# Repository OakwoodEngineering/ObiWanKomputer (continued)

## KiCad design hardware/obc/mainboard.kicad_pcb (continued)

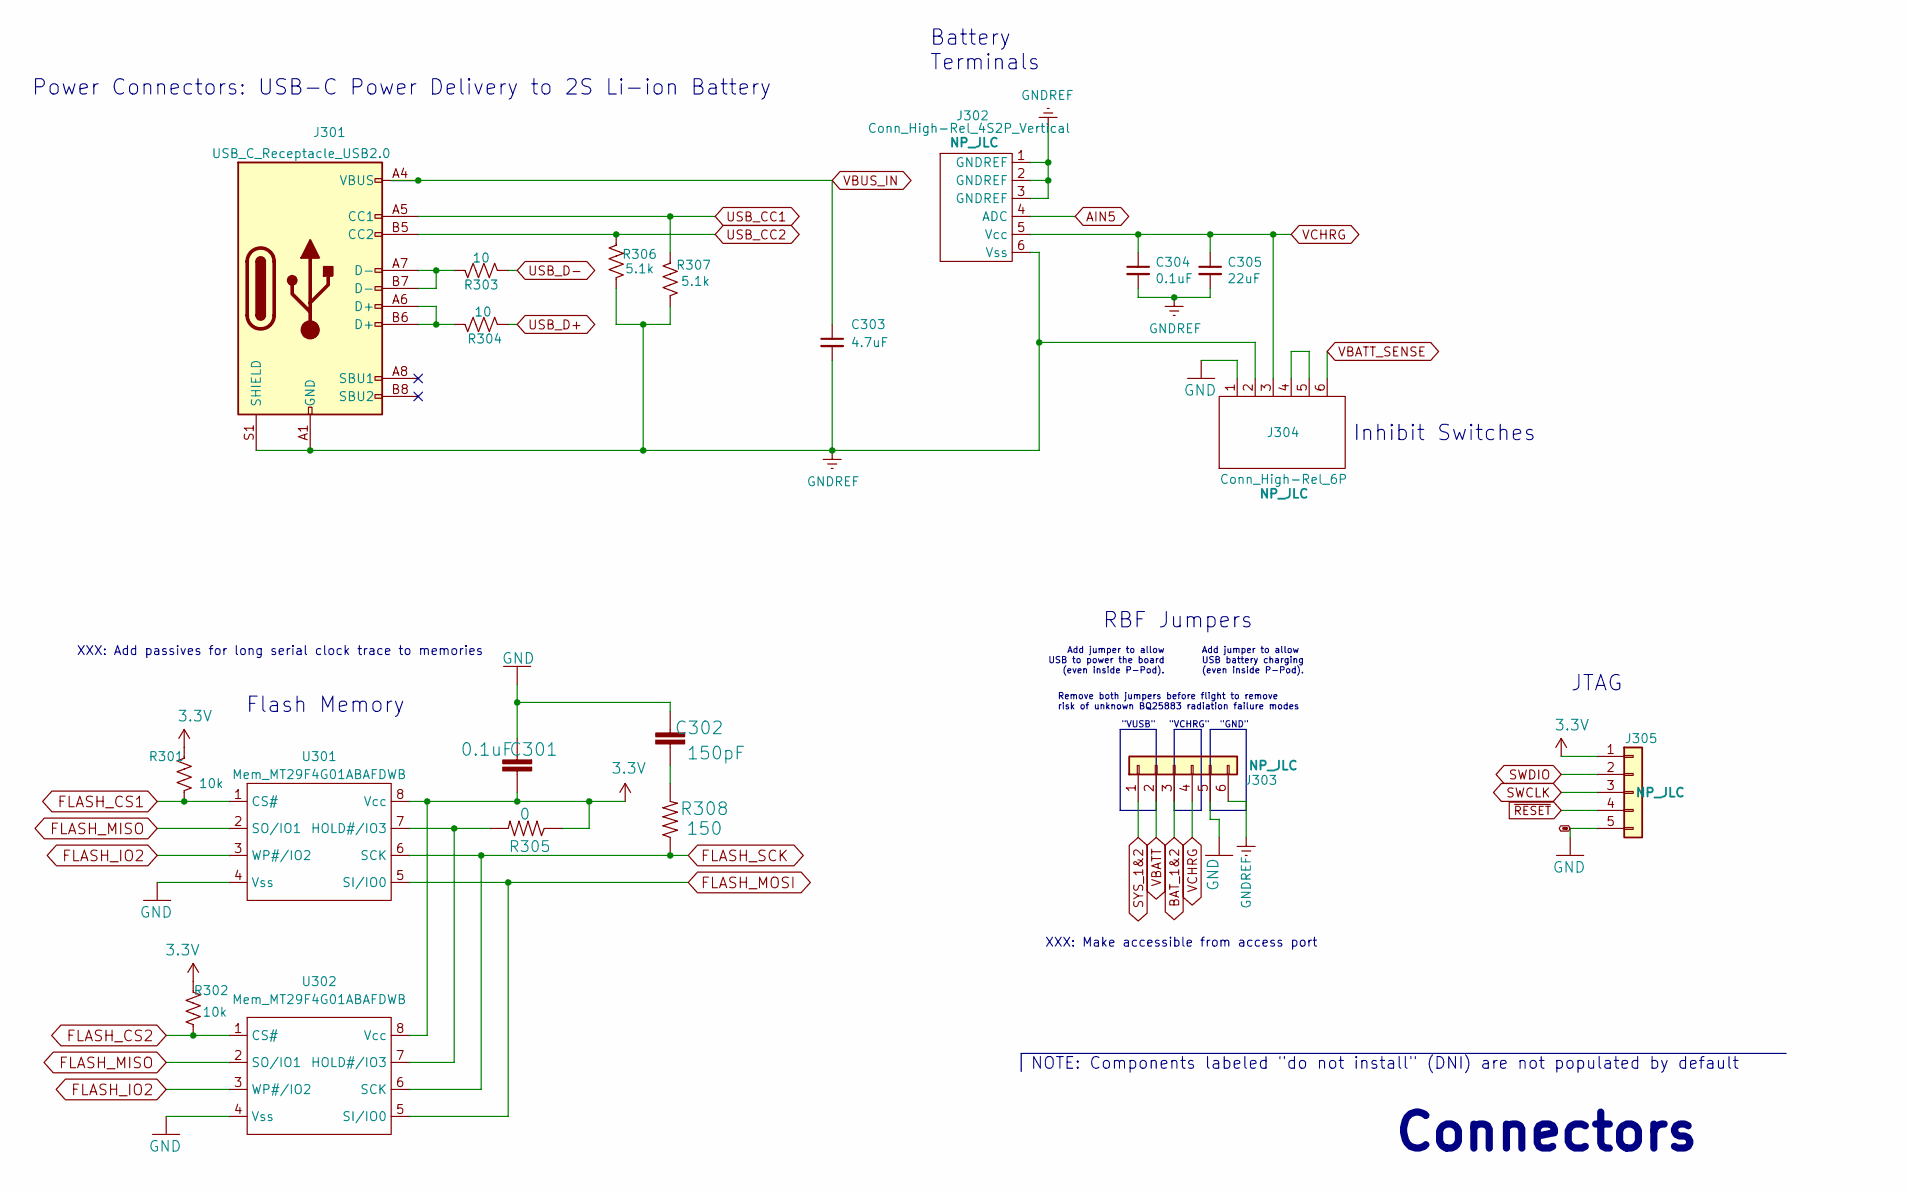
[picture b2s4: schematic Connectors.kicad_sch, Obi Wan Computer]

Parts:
C301, C304: 0.1uF; C_0603_1608Metric; Manufacturer_Part_Number CL10B104KB8NNNC; LCSC C1591
C302: 150pF; C_0603_1608Metric; Manufacturer_Part_Number CC0603JRNPO9BN151; LCSC C107038
C303: 4.7uF; C_0603_1608Metric; Manufacturer_Part_Number CL10A475KP8NNNC; LCSC C1705
C305: 22uF; C_0603_1608Metric; Manufacturer_Part_Number GRM188R61A226ME15D; LCSC C84419
J301: USB_C_Receptacle_USB2.0; USB_C_Receptacle_G-Switch_GT-USB-7010ASV; Manufacturer_Part_Number GT-USB-7010ASV; LCSC C2988369
J302: Conn_High-Rel_4S2P_Vertical; Harwin_G125-FV104F3-02AB000P_P1.25mm_Vertical; Manufacturer_Part_Number G125-FV104F3-02AB000P
J303: Conn_01x06; PinHeader_1x06_P2.54mm_Horizontal
J304: Conn_High-Rel_6P; MMCX-6_UMPT-06-01-L-RA-WT-TR_P2.0mm; Manufacturer_Part_Number UMPT-06-01-L-RA-WT-TR
J305: Conn_01x05; PinHeader_1x05_P2.54mm_Vertical
R301, R302: 10k; R_0603_1608Metric; Manufacturer_Part_Number ERJ3GEYJ103V; LCSC C169849
R303, R304: 10; R_0603_1608Metric; Manufacturer_Part_Number AC0603FR-0710RL; LCSC C138286
R305: 0; R_0603_1608Metric; Manufacturer_Part_Number MCT06030Z0000ZP500; LCSC C2654002
R306, R307: 5.1k; R_0603_1608Metric; Manufacturer_Part_Number RC0603FR-075K1L; LCSC C105580
R308: 150; R_0603_1608Metric; Manufacturer_Part_Number ERJ3RBD1500V; LCSC C336847
U301, U302: Mem_MT29F4G01ABAFDWB; UPDFN-8_8.0x6.0mm_P1.27mm; Manufacturer_Part_Number MT29F4G01ABAFDWB-IT:F; LCSC C2909506

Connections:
3.3V: C301.1, J305.1, R301.2, R302.2, R305.1, U301.8 (Vcc), U302.8 (Vcc); also elsewhere on the board
AIN5: J302.4 (ADC); also elsewhere on the board
BAT_1&2: J303.3; also elsewhere on the board
FLASH_CS1: R301.1, U301.1 (CS#); also elsewhere on the board
FLASH_CS2: R302.1, U302.1 (CS#); also elsewhere on the board
FLASH_IO2: U301.3 (WP#/IO2), U302.3 (WP#/IO2); also elsewhere on the board
FLASH_MISO: U301.2 (SO/IO1), U302.2 (SO/IO1); also elsewhere on the board
FLASH_MOSI: U301.5 (SI/IO0), U302.5 (SI/IO0); also elsewhere on the board
FLASH_SCK: R308.1, U301.6 (SCK), U302.6 (SCK); also elsewhere on the board
GND: C301.2, C302.2, J303.5, J304.1, J305.5, U301.4 (Vss), U302.4 (Vss); also elsewhere on the board
GNDREF: C303.2, C304.2, C305.2, J301.A1 (GND), J301.A12 (GND), J301.B1 (GND), J301.B12 (GND), J301.S1 (SHIELD), J302.1 (GNDREF), J302.2 (GNDREF), J302.3 (GNDREF), J302.6 (Vss), J303.6, J304.2, R306.1, R307.1; also elsewhere on the board
unnamed: C302.1, R308.2
unnamed: J301.A6 (D+), J301.B6 (D+), R304.2
unnamed: J301.A7 (D-), J301.B7 (D-), R303.2
unnamed: J304.4, J304.5
unnamed: R305.2, U301.7 (HOLD#/IO3), U302.7 (HOLD#/IO3)
SWCLK: J305.3; also elsewhere on the board
SWDIO: J305.2; also elsewhere on the board
SYS_1&2: J303.1; also elsewhere on the board
USB_CC1: J301.A5 (CC1), R307.2
USB_CC2: J301.B5 (CC2), R306.2
USB_D+: R304.1; also elsewhere on the board
USB_D-: R303.1; also elsewhere on the board
VBATT: J303.2; also elsewhere on the board
VBATT_SENSE: J304.6; also elsewhere on the board
VBUS_IN: C303.1, J301.A4 (VBUS), J301.A9 (VBUS), J301.B4 (VBUS), J301.B9 (VBUS); also elsewhere on the board
VCHRG: C304.1, C305.1, J302.5 (Vcc), J303.4, J304.3
~RESET: J305.4; also elsewhere on the board

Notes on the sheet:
NOTE: Components labeled "do not install" (DNI) are not populated by default
XXX: Add passives for long serial clock trace to memories
Add jumper to allow USB battery charging (even inside P-Pod).
Remove both jumpers before flight to remove risk of unknown BQ25883 radiation failure modes
Connectors
Flash Memory
Battery Terminals
"VCHRG"
XXX: Make accessible from access port
RBF Jumpers
Power Connectors: USB-C Power Delivery to 2S Li-ion Battery
"GND"
Inhibit Switches
Add jumper to allow USB to power the board (even inside P-Pod).
"VUSB"
JTAG

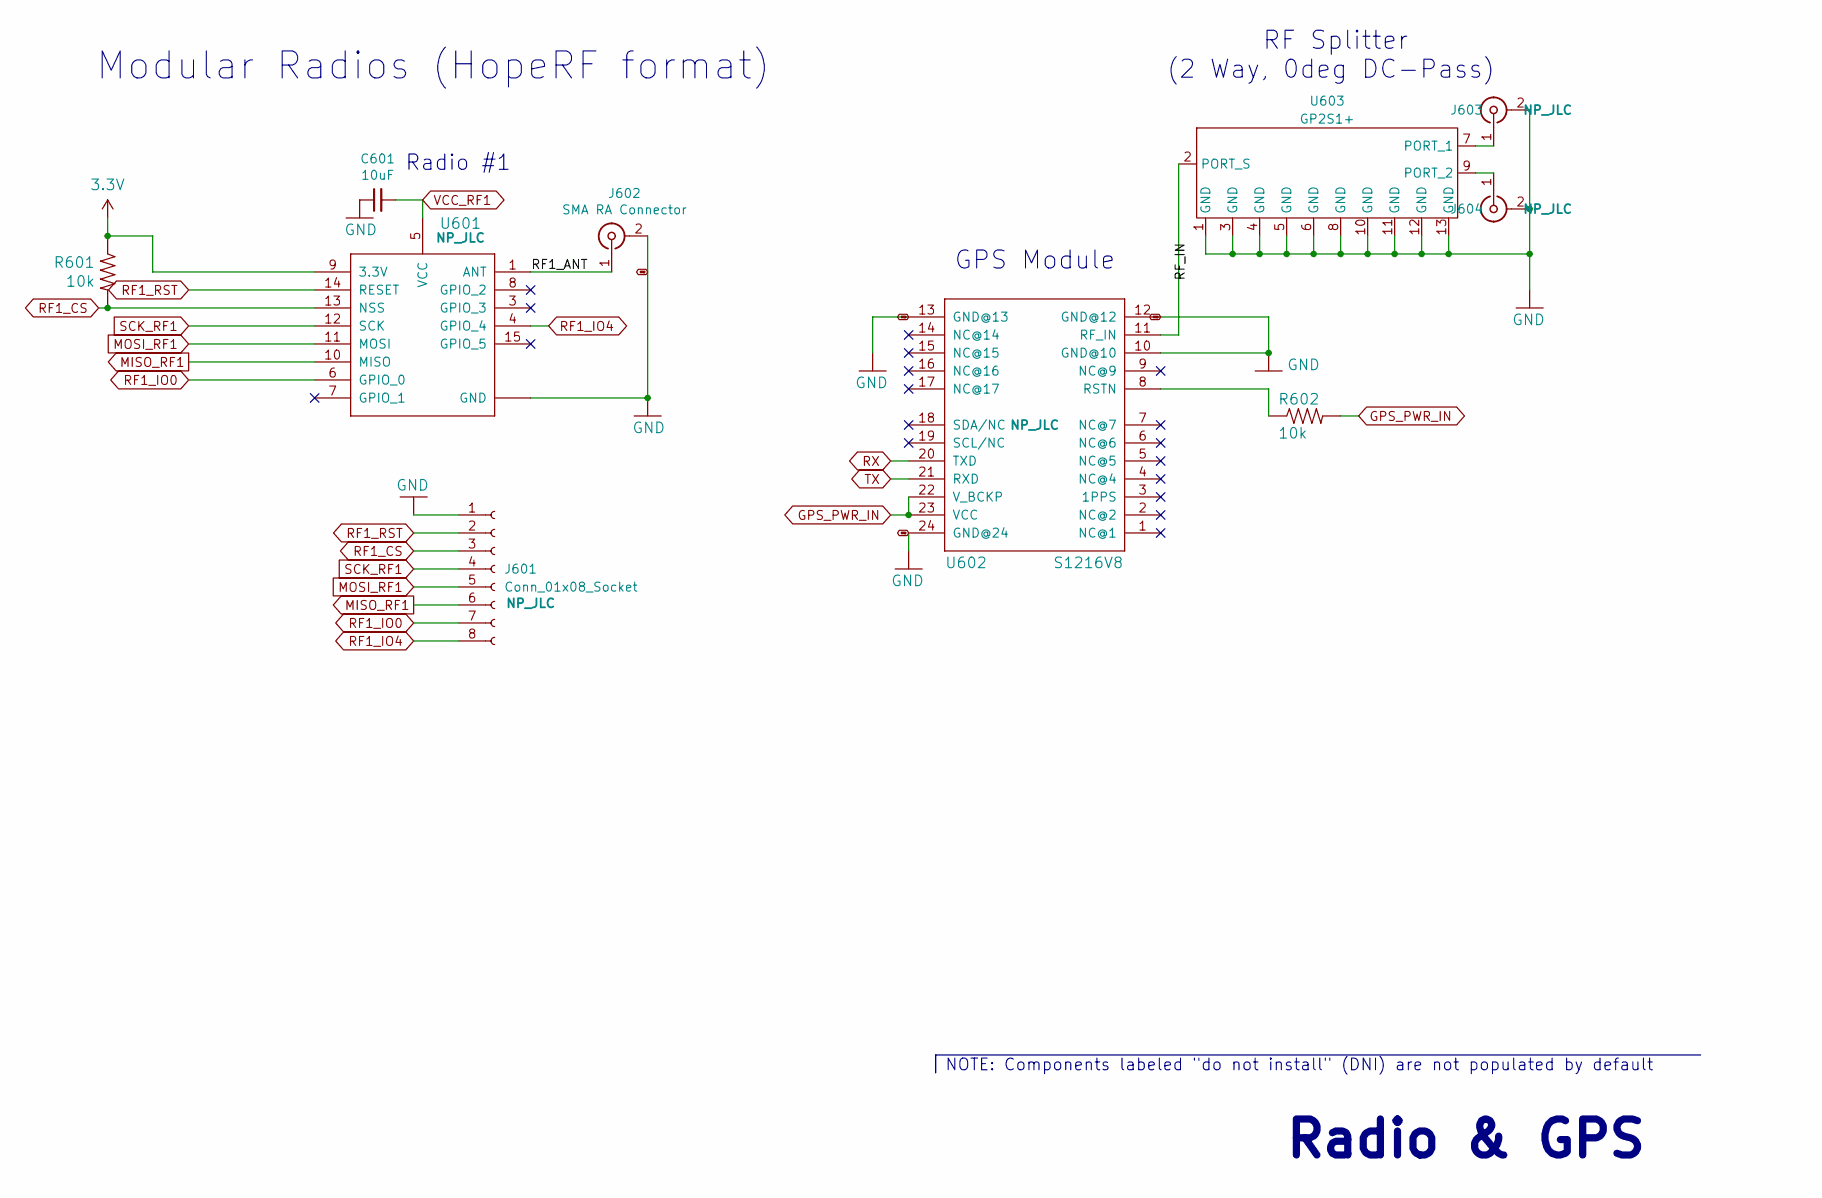
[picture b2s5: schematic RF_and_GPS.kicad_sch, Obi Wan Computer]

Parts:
C601: 10uF; C_0603_1608Metric; Manufacturer_Part_Number CL10A106MP8NNNC; LCSC C85713
J601: Conn_01x08_Socket; PinSocket_1x08_P2.54mm_Vertical
J602, J603, J604: SMA RA Connector; SAMTEC_MMCXV-J-P-HF-ST-EM1; Manufacturer_Part_Number MMCXV-J-P-HF-ST-EM1-ND
R601, R602: 10k; R_0603_1608Metric; Manufacturer_Part_Number ERJ3GEYJ103V; LCSC C169849
U601: RFM98PW; RFM95PW; Manufacturer_Part_Number RFM98PW
U602: S1216V8; S1216_24PIN_PACKAGE; Manufacturer_Part_Number S1216V8
U603: GP2S1+; DQ1225-12-1EP_3.0x3.0mm_P0.51mm; Manufacturer_Part_Number GP2S1+; LCSC C879828

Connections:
3.3V: R601.1, U601.9 (3.3V); also elsewhere on the board
/RF and GPS/RF1_ANT: J602.1 (In), U601.1 (ANT)
GND: C601.1, J601.1, J602.2 (Ext), J603.2 (Ext), J604.2 (Ext), U601.2 (GND), U601.16 (GND), U601.17 (GND), U602.10 (GND@10), U602.12 (GND@12), U602.13 (GND@13), U602.24 (GND@24), U603.1 (GND), U603.3 (GND), U603.4 (GND), U603.5 (GND), U603.6 (GND), U603.8 (GND), U603.10 (GND), U603.11 (GND), U603.12 (GND), U603.13 (GND); also elsewhere on the board
GPS_PWR_IN: R602.2, U602.22 (V_BCKP), U602.23 (VCC); also elsewhere on the board
MISO_RF1: J601.6, U601.10 (MISO); also elsewhere on the board
MOSI_RF1: J601.5, U601.11 (MOSI); also elsewhere on the board
unnamed: J603.1 (In), U603.7 (PORT_1)
unnamed: J604.1 (In), U603.9 (PORT_2)
unnamed: U602.11 (RF_IN), U603.2 (PORT_S)
unnamed: R602.1, U602.8 (RSTN)
RF1_CS: J601.3, R601.2, U601.13 (NSS); also elsewhere on the board
RF1_IO0: J601.7, U601.6 (GPIO_0); also elsewhere on the board
RF1_IO4: J601.8, U601.4 (GPIO_4); also elsewhere on the board
RF1_RST: J601.2, U601.14 (RESET); also elsewhere on the board
RX: U602.20 (TXD); also elsewhere on the board
SCK_RF1: J601.4, U601.12 (SCK); also elsewhere on the board
TX: U602.21 (RXD); also elsewhere on the board
VCC_RF1: C601.2, U601.5 (VCC); also elsewhere on the board

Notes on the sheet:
RF Splitter (2 Way, 0deg DC-Pass)
Modular Radios (HopeRF format)
Radio & GPS
NOTE: Components labeled "do not install" (DNI) are not populated by default
Radio #1
GPS Module

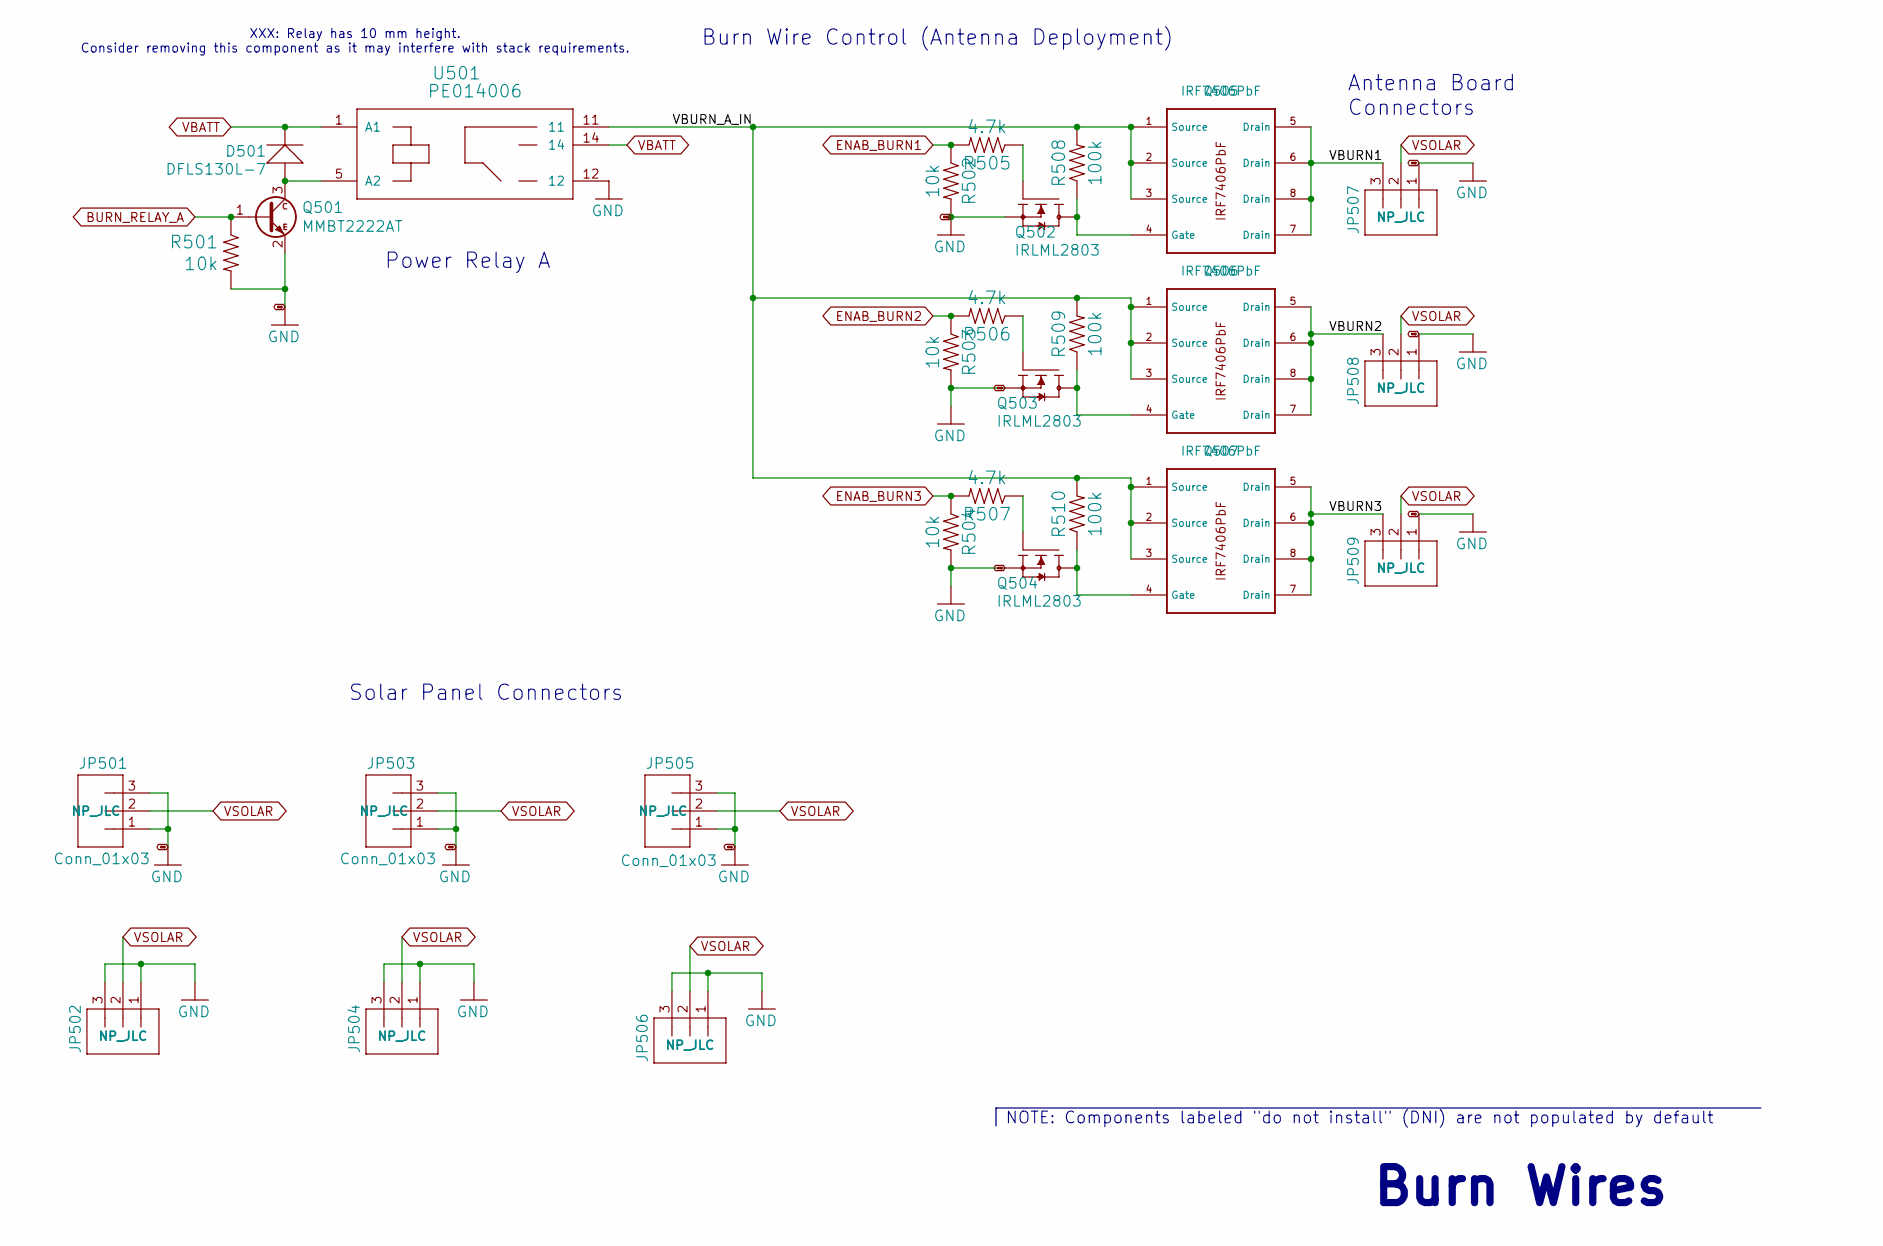
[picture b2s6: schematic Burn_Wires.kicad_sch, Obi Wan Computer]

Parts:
D501: DFLS130L-7; D_SOD-123; Manufacturer_Part_Number DFLS130L-7; LCSC C110493
JP501, JP502, JP503, JP504, JP505, JP506, JP507, JP508, JP509: Conn_01x03; CONN_22-11-2032_MOL; Manufacturer_Part_Number 0022112032
Q501: MMBT2222AT; SOT-23; Manufacturer_Part_Number MMBT2222ALT1G; LCSC C82460
Q502, Q503, Q504: IRLML2803; SOT-23; Manufacturer_Part_Number IRLML2803TRPBF; LCSC C2590
Q505, Q506, Q507: IRF7406PbF; SO-8_3.9x4.9mm_P1.27mm; Manufacturer_Part_Number IRF7406TRPBF; LCSC C169769
R501, R502, R503, R504: 10k; R_0603_1608Metric; Manufacturer_Part_Number ERJ3GEYJ103V; LCSC C169849
R505, R506, R507: 4.7k; R_0603_1608Metric; Manufacturer_Part_Number 0603WAF4701T5E; LCSC C23162
R508, R509, R510: 100k; R_0603_1608Metric; Manufacturer_Part_Number CRCW0603100KFKEC; LCSC C5369222
U501: PE014006; RELAY_PE014006_REV-SSE; Manufacturer_Part_Number PE014006 TE

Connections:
/Burn Wires/VBURN1: JP507.3, Q505.5 (Drain), Q505.6 (Drain), Q505.7 (Drain), Q505.8 (Drain)
/Burn Wires/VBURN2: JP508.3, Q506.5 (Drain), Q506.6 (Drain), Q506.7 (Drain), Q506.8 (Drain)
/Burn Wires/VBURN3: JP509.3, Q507.5 (Drain), Q507.6 (Drain), Q507.7 (Drain), Q507.8 (Drain)
/Burn Wires/VBURN_A_IN: Q505.1 (Source), Q505.2 (Source), Q505.3 (Source), Q506.1 (Source), Q506.2 (Source), Q506.3 (Source), Q507.1 (Source), Q507.2 (Source), Q507.3 (Source), R508.2, R509.2, R510.2, U501.11
BURN_RELAY_A: Q501.1 (B), R501.1; also elsewhere on the board
ENAB_BURN1: R502.1, R505.2; also elsewhere on the board
ENAB_BURN2: R503.1, R506.2; also elsewhere on the board
ENAB_BURN3: R504.1, R507.2; also elsewhere on the board
GND: JP501.1, JP501.3, JP502.1, JP502.3, JP503.1, JP503.3, JP504.1, JP504.3, JP505.1, JP505.3, JP506.1, JP506.3, JP507.1, JP508.1, JP509.1, Q501.2 (E), Q502.2 (S), Q503.2 (S), Q504.2 (S), R501.2, R502.2, R503.2, R504.2, U501.12; also elsewhere on the board
unnamed: D501.A, Q501.3 (C), U501.5 (A2)
unnamed: Q502.3 (D), Q505.4 (Gate), R508.1
unnamed: Q502.1 (G), R505.1
unnamed: Q503.3 (D), Q506.4 (Gate), R509.1
unnamed: Q503.1 (G), R506.1
unnamed: Q504.3 (D), Q507.4 (Gate), R510.1
unnamed: Q504.1 (G), R507.1
VBATT: D501.C, U501.1 (A1), U501.14; also elsewhere on the board
VSOLAR: JP501.2, JP502.2, JP503.2, JP504.2, JP505.2, JP506.2, JP507.2, JP508.2, JP509.2; also elsewhere on the board

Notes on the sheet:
Antenna Board Connectors
Burn Wires
XXX: Relay has 10 mm height. Consider removing this component as it may interfere with stack requirements.
Burn Wire Control (Antenna Deployment)
Solar Panel Connectors
Power Relay A
NOTE: Components labeled "do not install" (DNI) are not populated by default

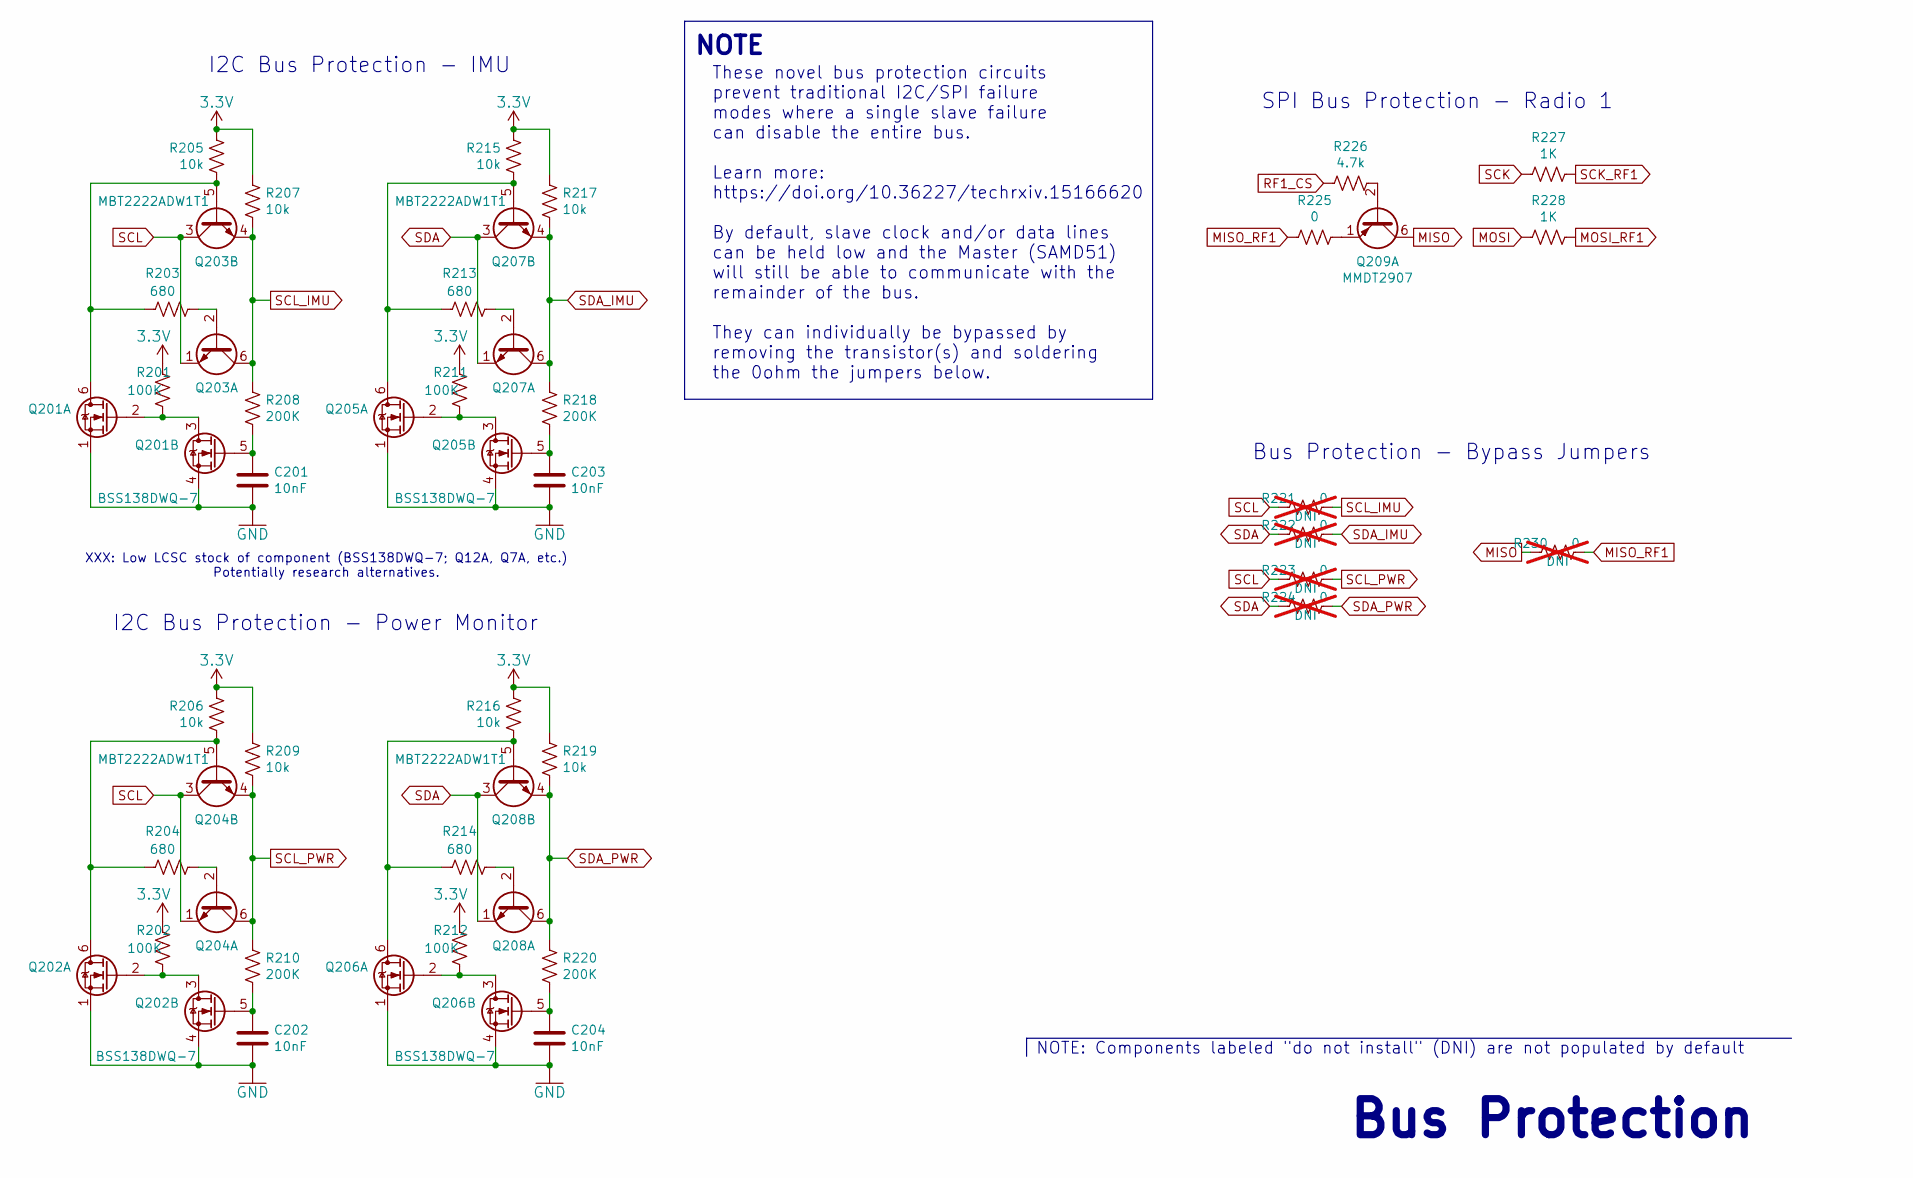
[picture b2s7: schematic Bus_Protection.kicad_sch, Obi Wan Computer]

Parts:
C201, C202, C203, C204: 10nF; C_0603_1608Metric; Manufacturer_Part_Number CL10B103KB8NNNC; LCSC C1589
Q201, Q202, Q205, Q206: BSS138DWQ-7; SOT-363_SC-70-6; Manufacturer_Part_Number BSS138DWQ-7; LCSC C3280240
Q203, Q204, Q207, Q208: MBT2222ADW1T1; SOT-363_SC-70-6; Manufacturer_Part_Number MBT2222ADW1T1G; LCSC C157366
Q209: MMDT2907; SOT-363_SC-70-6; Manufacturer_Part_Number MMDT2907AQ-7-F; LCSC C526684
R201, R202, R211, R212: 100K; R_0603_1608Metric; Manufacturer_Part_Number CRCW0603100KFKEC; LCSC C5369222
R203, R204, R213, R214: 680; R_0603_1608Metric; Manufacturer_Part_Number CRCW0603680RJNEA; LCSC C4244464
R205, R206, R207, R209, R215, R216, R217, R219: 10k; R_0603_1608Metric; Manufacturer_Part_Number ERJ3GEYJ103V; LCSC C169849
R208, R210, R218, R220: 200K; R_0603_1608Metric; Manufacturer_Part_Number ERA3AEB204V; LCSC C473261
R221, R222, R223, R224, R230: 0; R_0603_1608Metric; Manufacturer_Part_Number MCT06030Z0000ZP500; not fitted
R225: 0; R_0603_1608Metric; Manufacturer_Part_Number MCT06030Z0000ZP500; LCSC C2654002
R226: 4.7k; R_0603_1608Metric; Manufacturer_Part_Number 0603WAF4701T5E; LCSC C23162
R227, R228: 1K; R_0603_1608Metric; Manufacturer_Part_Number CRCW06031K00FKEAC; LCSC C844746

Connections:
3.3V: R201.1, R202.1, R205.1, R206.1, R207.1, R209.1, R211.1, R212.1, R215.1, R216.1, R217.1, R219.1; also elsewhere on the board
GND: C201.2, C202.2, C203.2, C204.2, Q201.1 (S2), Q201.4 (S1), Q202.1 (S2), Q202.4 (S1), Q205.1 (S2), Q205.4 (S1), Q206.1 (S2), Q206.4 (S1); also elsewhere on the board
MISO: Q209.6 (C1), R230.2; also elsewhere on the board
MISO_RF1: R225.2, R230.1; also elsewhere on the board
MOSI: R228.1; also elsewhere on the board
MOSI_RF1: R228.2; also elsewhere on the board
unnamed: Q201.6 (D1), Q203.5 (B2), R203.2, R205.2
unnamed: Q201.2 (G2), Q201.3 (D2), R201.2
unnamed: C201.1, Q201.5 (G1), R208.2
unnamed: Q202.6 (D1), Q204.5 (B2), R204.2, R206.2
unnamed: Q202.2 (G2), Q202.3 (D2), R202.2
unnamed: C202.1, Q202.5 (G1), R210.2
unnamed: Q203.2 (B1), R203.1
unnamed: Q204.2 (B1), R204.1
unnamed: Q205.6 (D1), Q207.5 (B2), R213.2, R215.2
unnamed: Q205.2 (G2), Q205.3 (D2), R211.2
unnamed: C203.1, Q205.5 (G1), R218.2
unnamed: Q206.6 (D1), Q208.5 (B2), R214.2, R216.2
unnamed: Q206.2 (G2), Q206.3 (D2), R212.2
unnamed: C204.1, Q206.5 (G1), R220.2
unnamed: Q207.2 (B1), R213.1
unnamed: Q208.2 (B1), R214.1
unnamed: Q209.2 (B1), R226.1
unnamed: Q209.1 (E1), R225.1
RF1_CS: R226.2; also elsewhere on the board
SCK: R227.2; also elsewhere on the board
SCK_RF1: R227.1; also elsewhere on the board
SCL: Q203.1 (E1), Q203.3 (C2), Q204.1 (E1), Q204.3 (C2), R221.2, R223.2; also elsewhere on the board
SCL_IMU: Q203.4 (E2), Q203.6 (C1), R207.2, R208.1, R221.1; also elsewhere on the board
SCL_PWR: Q204.4 (E2), Q204.6 (C1), R209.2, R210.1, R223.1; also elsewhere on the board
SDA: Q207.1 (E1), Q207.3 (C2), Q208.1 (E1), Q208.3 (C2), R222.2, R224.2; also elsewhere on the board
SDA_IMU: Q207.4 (E2), Q207.6 (C1), R217.2, R218.1, R222.1; also elsewhere on the board
SDA_PWR: Q208.4 (E2), Q208.6 (C1), R219.2, R220.1, R224.1; also elsewhere on the board

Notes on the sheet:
These novel bus protection circuits prevent traditional I2C/SPI failure modes where a single slave failure can disable the entire bus. Learn more: https://doi.org/10.36227/techrxiv.15166620 By default, slave clock and/or data lines can be held low and the Master (SAMD51) will still be able to commu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
SPI Bus Protection - Radio 1
NOTE: Components labeled "do not install" (DNI) are not populated by default
NOTE
XXX: Low LCSC stock of component (BSS138DWQ-7; Q12A, Q7A, etc.) Potentially research alternatives.
Bus Protection
I2C Bus Protection - Power Monitor
I2C Bus Protection - IMU
Bus Protection - Bypass Jumpers

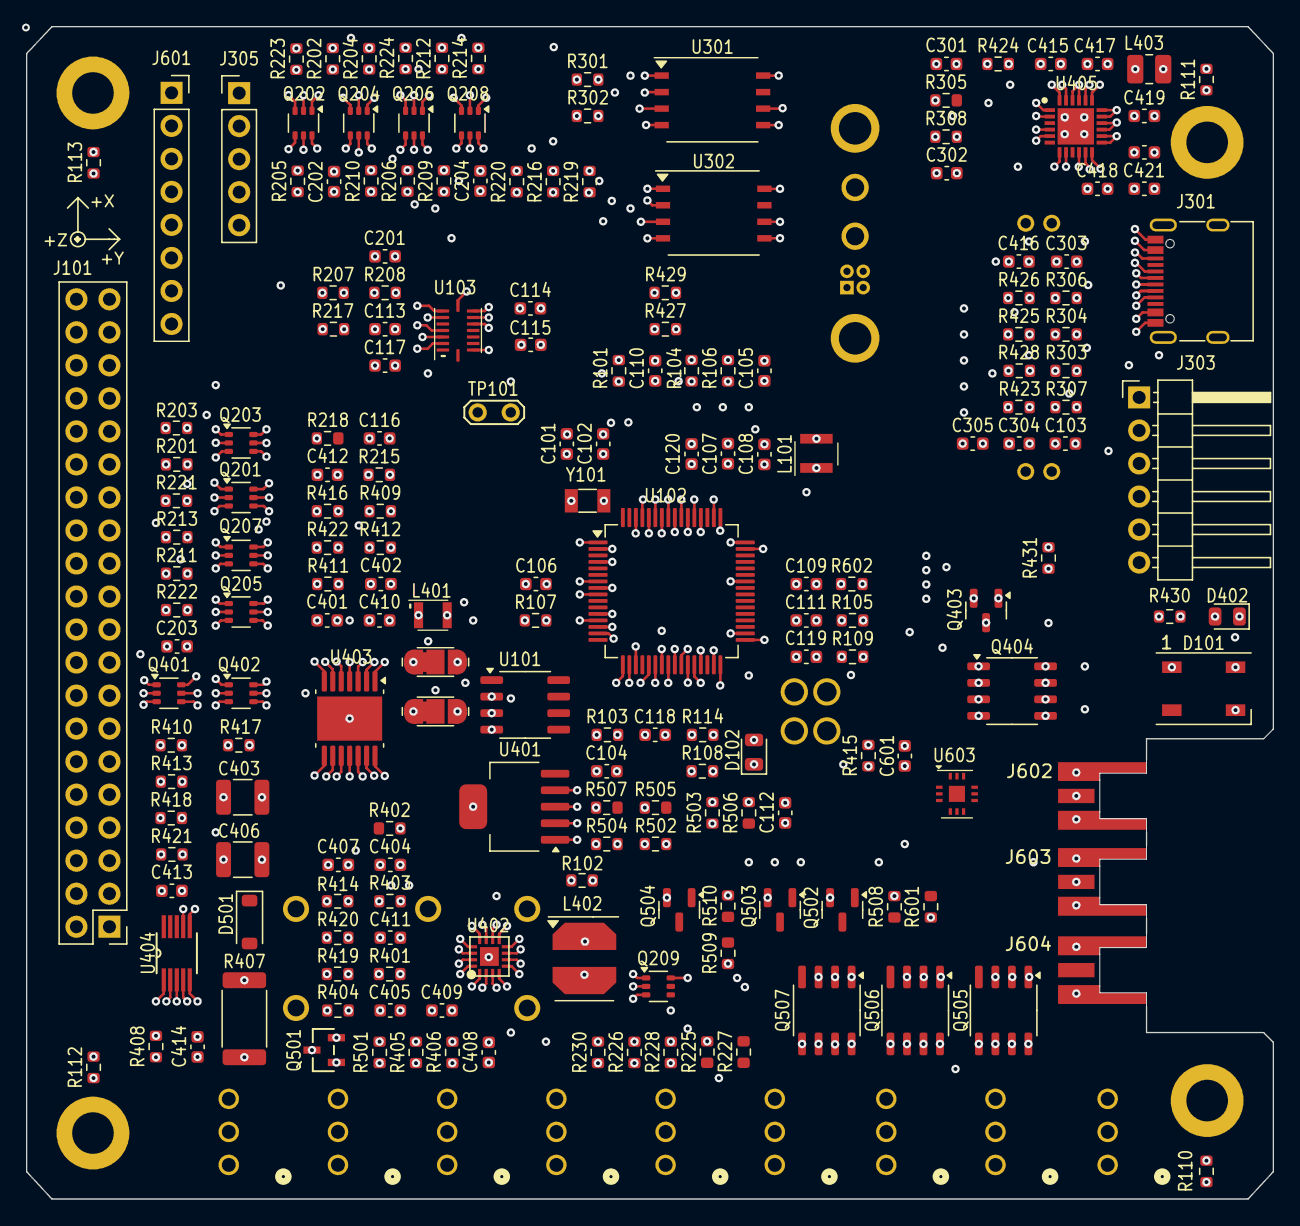
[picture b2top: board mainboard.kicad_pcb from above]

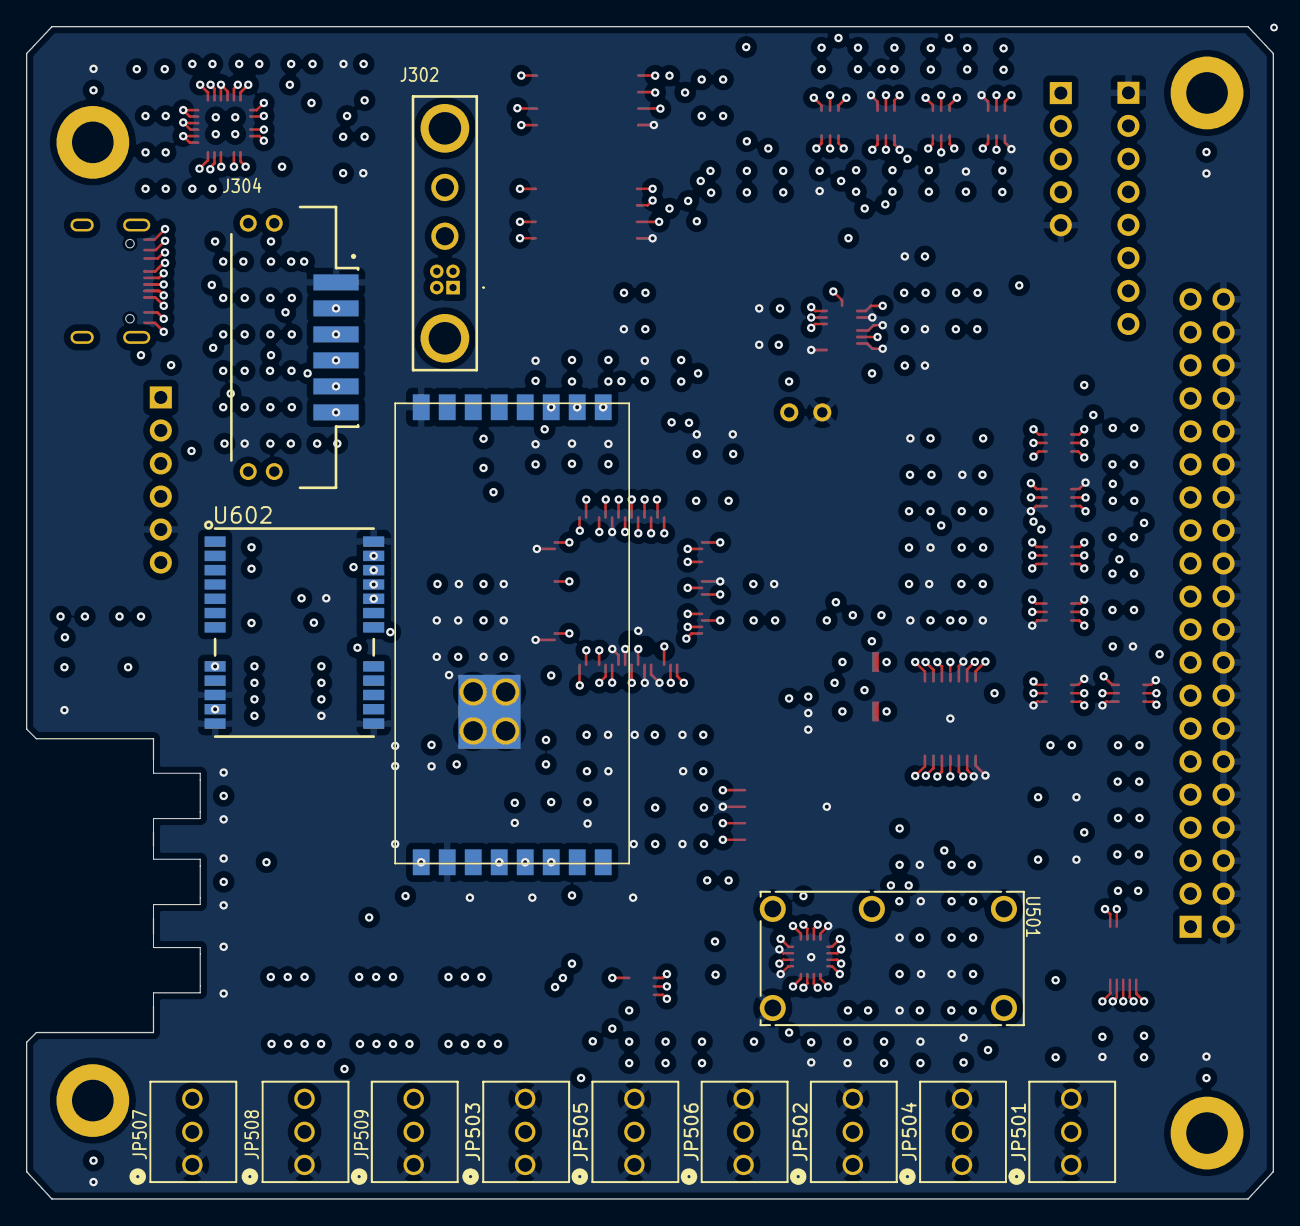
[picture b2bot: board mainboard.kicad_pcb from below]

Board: 6 copper layers, 95.9 x 90.2 mm, 214 parts (14 on the bottom side), 153 nets.

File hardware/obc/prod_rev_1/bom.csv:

Designator,Footprint,Quantity,Value,LCSC Part #
"C101, C102",0603,2,8pF,C1882476
"C103, C104, C106, C107, C113, C114, C118, C119, C120, C301, C304, C407",0603,12,0.1uF,C1591
"C105, C108, C109, C111, C115, C116, C412, C415",0603,8,1uF,C59782
"C110, C112, C117, C404, C405, C413, C417, C421, C601",0603,9,10uF,C85713
"C201, C202, C203, C204",0603,4,10nF,C1589
C302,0603,1,150pF,C107038
"C303, C416",0603,2,4.7uF,C1705
"C305, C401, C402, C411, C419, C420",0603,6,22uF,C84419
"C403, C406",1210,2,100uF,C90143
C408,0603,1,2.2uF,C23630
C409,0603,1,22nF,C21122
"C410, C414",0603,2,3.3nF,C1613
C418,0603,1,47nF,C1622
D101,LED_WS2812B_PLCC4_5.0x5.0mm_P3.2mm,1, WS2812B-B/W,C114586
D102,0805,1,RED,C142306
D402,0805,1,GREEN,C2297
D501,D_SOD-123,1,DFLS130L-7,C110493
"H101, H102, H103, H104",MountingHole_3.2mm_M3_DIN965_Pad,4,MountingHole_Pad,
J101,PinHeader_2x20_P2.54mm_Vertical,1,Conn_02x20_Odd_Even,
J301,USB_C_Receptacle_G-Switch_GT-USB-7010ASV,1,USB_C_Receptacle_USB2.0,C2988369
J302,Harwin_G125-FV104F3-02AB000P_P1.25mm_Vertical,1,Conn_High-Rel_4S2P_Vertical,
J303,PinHeader_1x06_P2.54mm_Horizontal,1,Conn_01x06,
J304,MMCX-6_UMPT-06-01-L-RA-WT-TR_P2.0mm,1,Conn_High-Rel_6P,
J305,PinHeader_1x05_P2.54mm_Vertical,1,Conn_01x05,
"J602, J603, J604",SAMTEC_MMCXV-J-P-HF-ST-EM1,3,SMA RA Connector,
JP401,SolderJumper-3_P1.3mm_Bridged12_RoundedPad1.0x1.5mm,1,Jumper_3_Bridged12,
"JP501, JP502, JP503, JP504, JP505, JP506, JP507, JP508, JP509",CONN_22-11-2032_MOL,9,Conn_01x03,
L101,L_Sunlord_2.0x1.6mm,1,10uH,C370419
L401,L_TDK_1008_2.5x2.0mm,1,3.3uH,C404805
L402,TDK_1008_4.9x5.5mm,1,33uH,C2046704
L403,1008,1,1uH,C5247968
"Q201, Q202, Q205, Q206",SOT-363_SC-70-6,4,"BSS138PS,115",C193381
"Q203, Q204, Q207, Q208, Q401, Q402",SOT-363_SC-70-6,6,MBT2222ADW1T1,C157366
Q209,SOT-363_SC-70-6,1,"BC857BS,115",C8654
"Q403, Q502, Q503, Q504",SOT-23,4,IRLML2803,C2590
"Q404, Q505, Q506, Q507",SO-8_3.9x4.9mm_P1.27mm,4,IRF7406PbF,C169769
Q501,SOT-23,1,MMBT2222AT,C82460
R101,0603,1,680,
R102,0603,1,316K,C25814
R103,0603,1,110K,C137807
"R104, R105, R106, R108, R114, R205, R206, R207, R209, R215, R216, R217, R219, R301, R302, R402, R422, R426, R427, R430, R501, R502, R503, R504, R601, R602",0603,26,10k,C169849
"R107, R226, R423, R429, R505, R506, R507",0603,7,4.7k,C23162
"R109, R308",0603,2,150,C336847
"R110, R111, R112, R113",0603,4,DNI,
"R115, R116, R227, R228, R408",0603,5,1K,C844746
"R201, R202, R211, R212, R411, R413, R415, R416, R421, R508, R509, R510",0603,12,100K,C5369222
"R203, R204, R213, R214",0603,4,680,C112310
"R208, R210, R218, R220, R418",0603,5,200K,C473261
"R225, R305, R404",0603,3,0,C2654002
"R303, R304",0603,2,10, C138286
"R306, R307",0603,2,5.1k,C105580
R401,0603,1,107K,
"R403, R431",0603,2,3.3K,C108078
R405,0603,1,787K,C246008
R406,0603,1,121K,C861095
R407,2512,1,0.1,C165698
"R409, R410",0603,2,73.2K,C843966
R412,0603,1,22.1K,C137768
R414,0603,1,845K,C246013
R417,0603,1,20K,C105575
R419,0603,1,3.01K,C137732
R420,0603,1,2.1M,C2085910
R424,0603,1,5.23K,C227977
R425,0603,1,30.1K,C137745
R428,0603,1,3.16K,C185333
U101,SO-8_3.9x4.9mm_P1.27mm,1,MAX706RESA,C28380
U102,TQFP-64_10x10mm_P0.5mm,1,ATSAMD51J20A-AU,C619371
U103,LGA-16_4.5x3.0mm_P0.5mm,1,BMI088,
"U301, U302",UPDFN-8_8.0x6.0mm_P1.27mm,2,Mem_MT29F4G01ABAFDWB,C2909506
U401,SOT-223-6,1,TPS7A4501DCQT,C2869558
U402,QFN-16-1EP_3x3mm_P0.5mm_EP1.9x1.9mm_ThermalVias,1,LTC4121,C687336
U403,HTSSOP-14-1EP_4.4x5mm_P0.65mm_EP3.4x5mm_Mask3x3.1mm,1,TPS54226PWPRPWP14_2P31X2P46-L,C72066
U404,MSOP-10_3x3mm_P0.5mm,1,ADM1176-1ARMZ-R7,C657860
U405,QFN50P400X400X100-25N-D,1,BQ25886RGER,C2765094
U501,RELAY_PE014006_REV-SSE,1,PE014006,
U601,RFM95PW,1,RFM98PW,
U602,S1216_24PIN_PACKAGE,1,S1216V8,
U603,DQ1225-12-1EP_3.0x3.0mm_P0.51mm,1,GP2S1+,C879828
Y101,Crystal_SMD_3215-2Pin_3.2x1.5mm,1,32.768kHz,C32346
